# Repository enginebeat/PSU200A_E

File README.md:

# PSU200A_E
Graham's Power supply control Board

Changing to using Eagle and also go surface mount

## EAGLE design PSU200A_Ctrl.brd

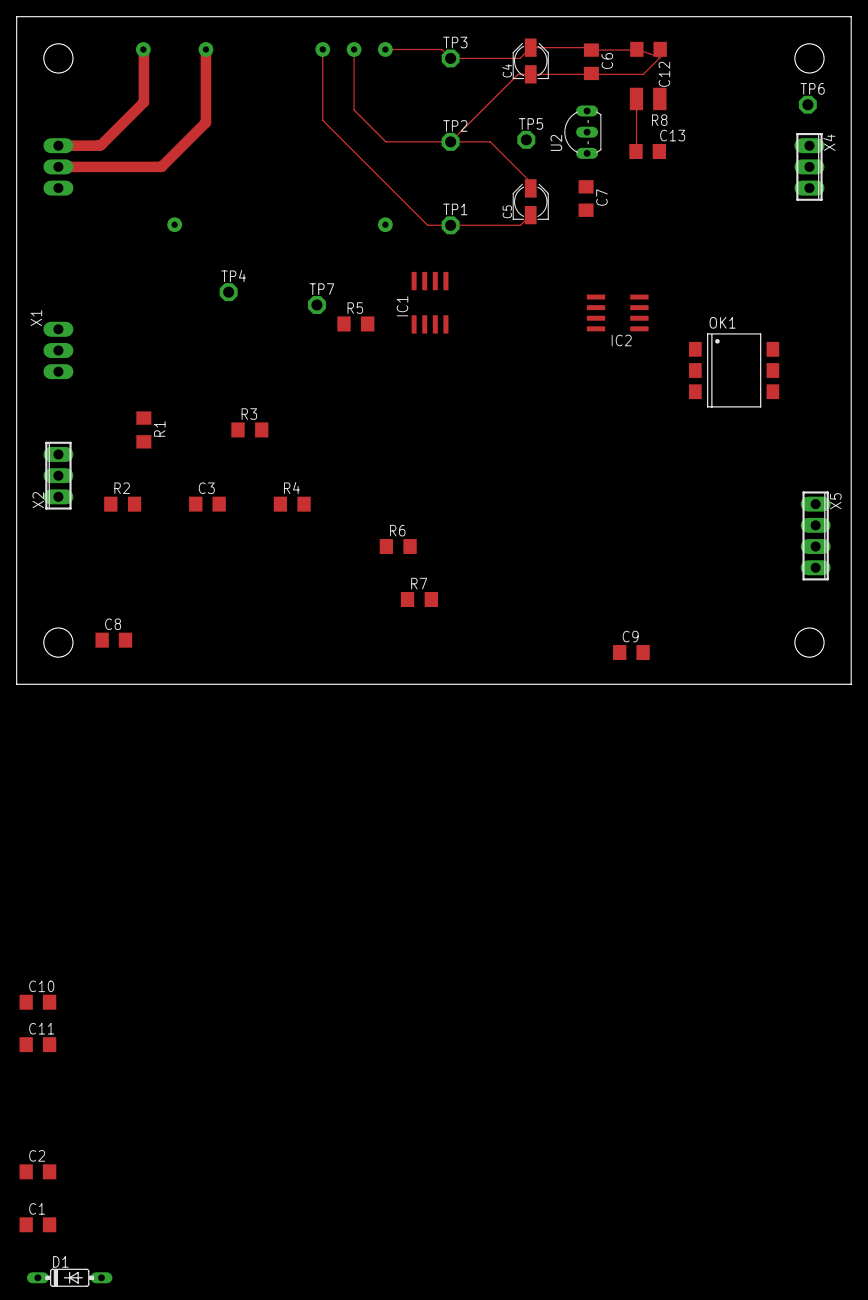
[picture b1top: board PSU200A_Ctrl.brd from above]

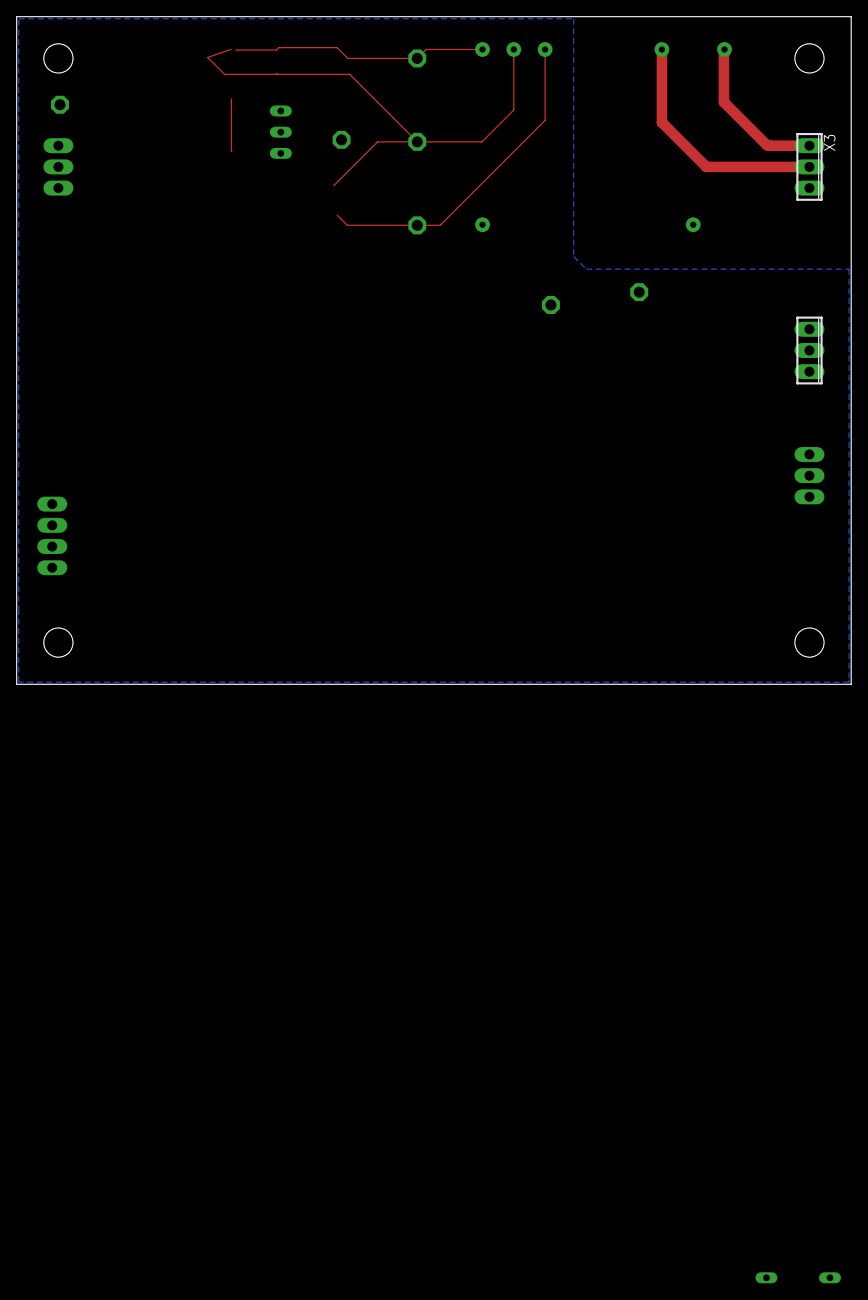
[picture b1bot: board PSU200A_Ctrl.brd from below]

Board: 2 copper layers, 100.0 x 80.0 mm, 39 parts (2 on the bottom side), 20 nets.

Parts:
C1, C2, C6, C7, C10, C11, C12, C13: 0.1u; C1206
C3: 2.2u; C1206
C4, C5: 22u; PANASONIC_B
C8, C9: 1n; C1206
D1: 1N4148DO35-7; DO35-7
IC1, IC2: LM358D; SO08
OK1: H11A1SM; DIL6-SMD
R1, R2, R5, R6, R7: 10k; R1206
R3: 1k; R1206
R4: 10K; R1206
R8: 1K; R1210
TP1, TP2, TP3, TP4, TP5, TP6, TP7: TPPAD1-13; P1-13
U1: TMPM04215; TMPM04XXX
U2: LM4040; TO92-
X1, X2, X3, X4: 3POL254
X5: 4POL254

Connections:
+10V: C13.1, R8.2, TP5.TP, U2.2, X1.1
+15V: C2.1, C4.+, C6.1, C10.1, C12.1, IC1.8, IC2.8, R8.1, TP3.TP, U1.P$3, X5.3
-15V: C1.1, C5.-, C7.2, C11.1, IC1.4, IC2.4, TP1.TP, U1.P$5, X5.4
GND: C1.2, C2.2, C4.-, C5.+, C6.2, C7.1, C10.2, C11.2, C12.2, C13.2, D1.C, IC1.5, IC2.3, IC2.5, OK1.1, TP2.TP, U1.P$4, U2.3, X1.3, X4.3
unnamed: IC1.3, X1.2
unnamed: IC1.1, IC1.2, R1.1, TP4.TP
unnamed: C3.1, IC1.6, R1.2, R2.2
unnamed: C3.2, IC1.7, R3.1
unnamed: R2.1, X2.1
unnamed: C9.1, IC2.7, R5.1, X2.3
unnamed: D1.A, OK1.2, R3.2, TP7.TP
unnamed: OK1.5, TP6.TP, X4.1
unnamed: OK1.4, X4.2
unnamed: R6.2, X5.1
unnamed: C8.2, IC2.2, R4.2, R6.1
unnamed: C8.1, IC2.1, R4.1, X2.2
unnamed: U1.P$7, X3.1
unnamed: U1.P$6, X3.2
unnamed: R7.2, X5.2
unnamed: C9.2, IC2.6, R5.2, R7.1

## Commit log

2020-02-19 schematic done
